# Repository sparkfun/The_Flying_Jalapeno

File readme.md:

The Flying Jalapeno
=======

This is a generic testbed board that will act as the "brain and usual hardware" for 99% of testbeds. We currently design a ton of testbeds using the pro mini, but this requires us to also put more circuitry on the testbed itself. Since we use basically the same extra stuff on every testbed, it makes sense to have a custom board that includes all of this.

It will be strictly used in QC and production (a sub assembly). 

The title "The Flying Jalapeno". I know I'm a dork, but hey, might as well name it something fun. And why not be in honor of the best AVC team name ever??

The extra hardware necessary for most testbeds:

-2 adjustable vregs with high-side switches
-2 resistor groups used for pre-testing for shorts to GND
-2 IOs setup for capsense (basically just 10M resistors for each "send" line)
-Resistors in place for PASS/FAIL leds
-Larger Vreg for VCC, to make more current available as needed
-Universal connector (2/18 header) that will mate with future pogobeds. (The idea here is that most future pogobeds will be comprised of two things: (2) the FLying Jalapeno and (2) the custom pogopin hardware.
-1x6 SMD FTDI RA header for easy programming and debug

License Information
-------------------

All of the designs in this repo are public domain but you buy me a beer if you use this and we meet someday ([Beerware license](http://en.wikipedia.org/wiki/Beerware)).

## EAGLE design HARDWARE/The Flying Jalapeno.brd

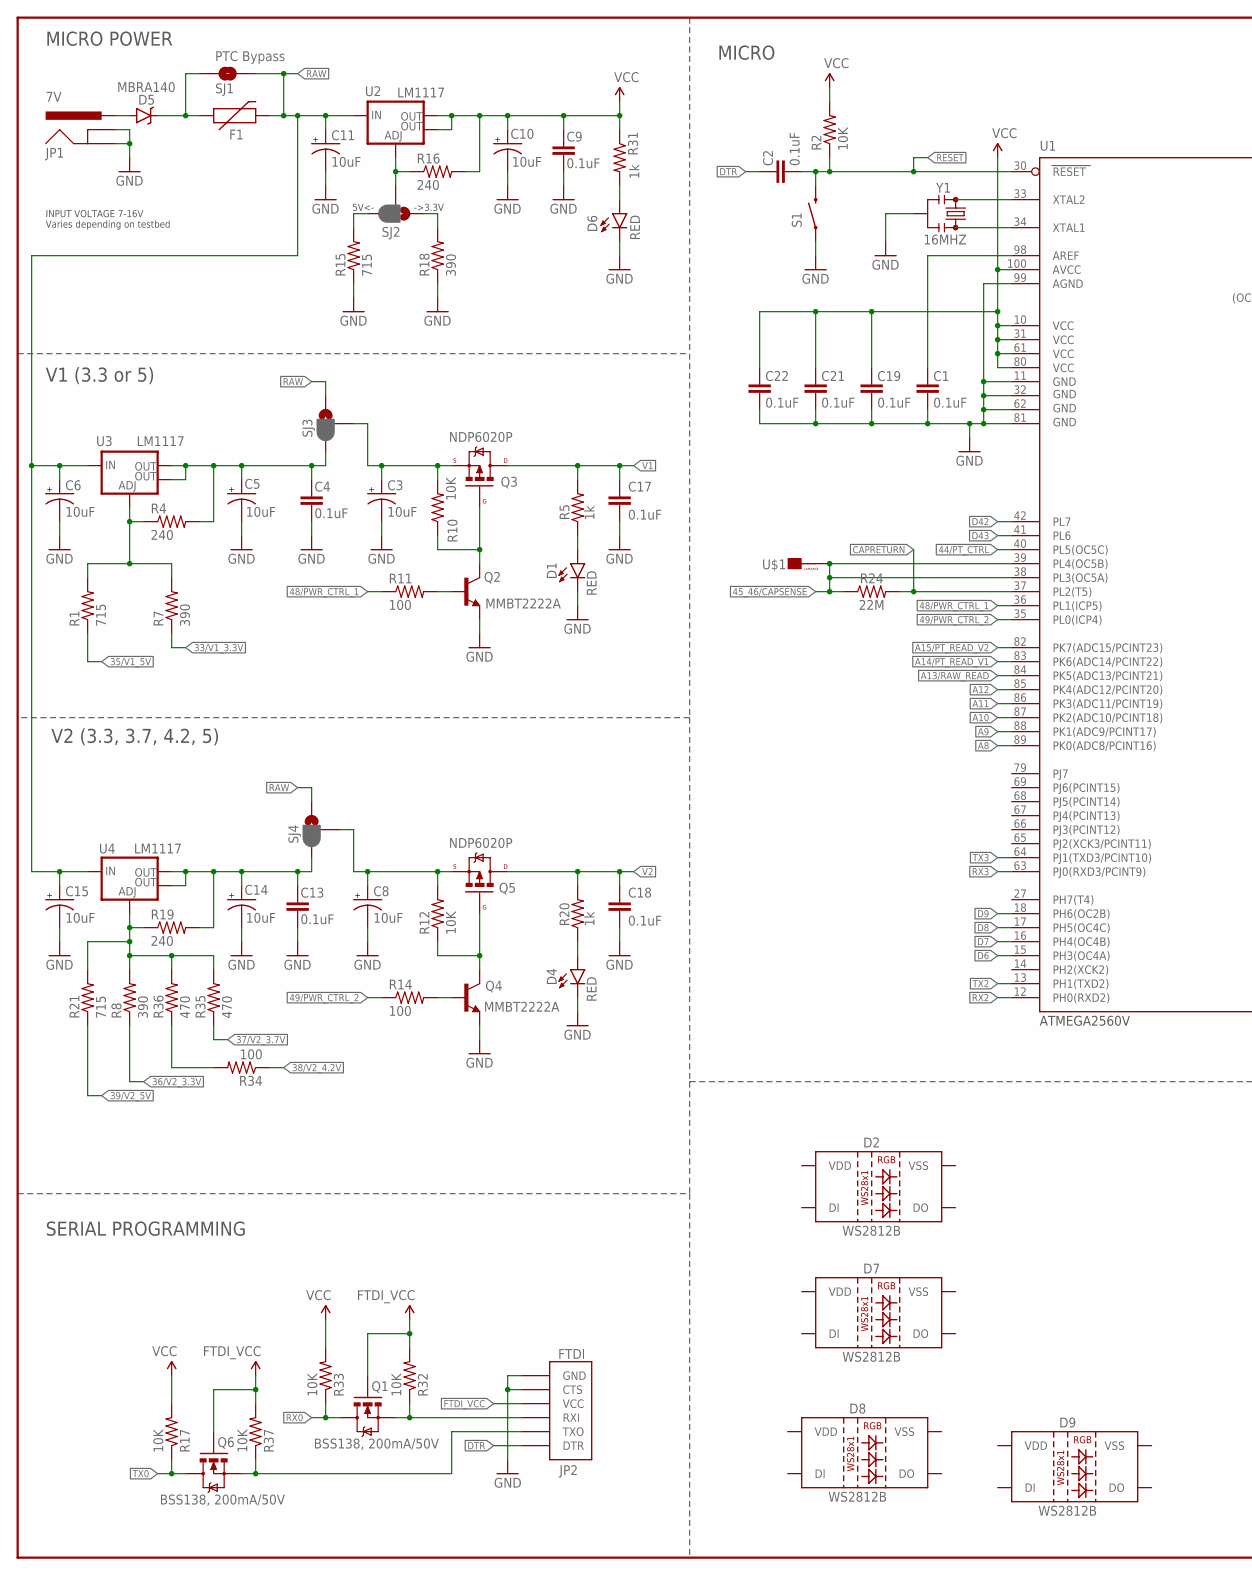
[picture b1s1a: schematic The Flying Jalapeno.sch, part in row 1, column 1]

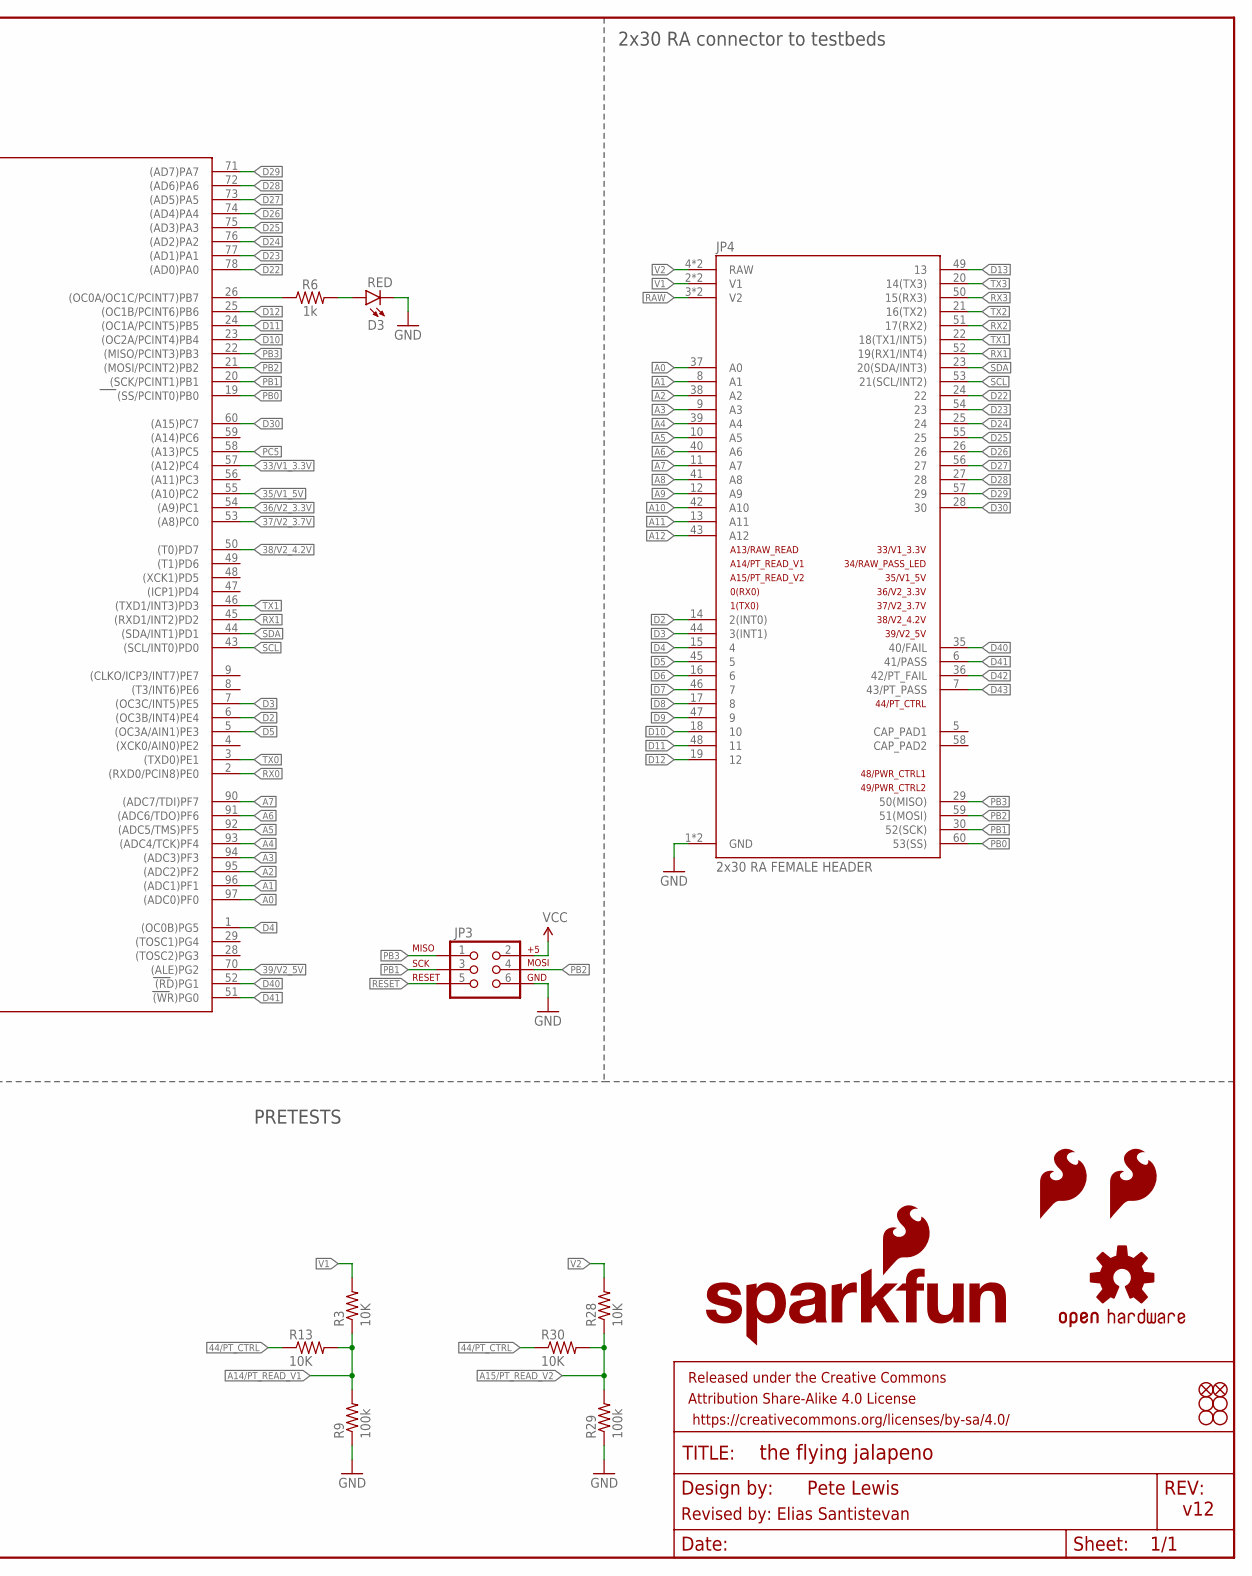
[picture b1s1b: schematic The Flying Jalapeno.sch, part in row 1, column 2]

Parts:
C1, C2, C4, C9, C13, C17, C18, C19, C21, C22: 0.1uF; 0603-CAP
C3, C8: 10uF; 0603-POLAR
C5, C6, C10, C11, C14, C15: 10uF; EIA3216@1
D1, D3, D4, D6: RED; LED-1206
D2, D7, D8, D9: WS2812B
D5: MBRA140; SMA-DIODE
F1: PTCTHERMISTOR1206; PTC-1206
FRAME1: FRAME-LEDGER; CREATIVE_COMMONS
JP1: 7V; POWER_JACK_PTH_LOCK
JP2: FTDI; FTDI_DEVICE_RA_SMT
JP3: AVR_SPI_PRG_6PTH; 2X3
JP4: 2x30 RA FEMALE HEADER; FLYING_JALAPENO_V3_F
JP5, JP8: FIDUCIALUFIDUCIAL; MICRO-FIDUCIAL
LOGO1: SFE_LOGO_NAME_FLAME.5_INCH; SFE_LOGO_NAME_FLAME_.5
LOGO2: SFE_LOGO_FLAME.3_INCH; SFE_LOGO_FLAME_.3
LOGO3: SFE_LOGO_FLAME.1_INCH; SFE_LOGO_FLAME_.1
LOGO4: OSHW-LOGOL; OSHW-LOGO-L
Q1, Q6: BSS138, 200mA/50V; SOT23-3
Q2, Q4: MMBT2222A; SOT23-3
Q3, Q5: NDP6020P; TO220V
R1, R15, R21: 715; 0603-RES
R2, R3, R10, R12, R13, R17, R28, R30, R32, R33, R37: 10K; 0603-RES
R4, R16, R19: 240; 0603-RES
R5, R6, R20, R31: 1k; 0603
R7, R8, R18: 390; 0603-RES
R9, R29: 100k; 0603-RES
R11, R14, R34: 100; 0603-RES
R24: 22M; 0603
R35, R36: 470; 0603-RES
S1: SWITCH-MOMENTARY-2SMD-REDUNDANT; TACTILE-SWITCH-SMD
SJ1: PTC Bypass; PAD-JUMPER-2-NO_NO_SILK
SJ2, SJ3, SJ4: JUMPER-PAD-3-2OF3_NC_BY_PASTE; PAD-JUMPER-3-2OF3_NC_BY_PASTE_YES_SILK_FULL_BOX
STANDOFF1, STANDOFF2, STANDOFF3, STANDOFF4: STAND-OFFTIGHT; STAND-OFF-TIGHT
U1: ATMEGA2560AU; TQFP100
U2, U3, U4: LM1117; SOT223
U$1: CAPSENSE_BUTTON_PAD_ONLY; CAPSENSE_BUTTON_PADS_ONLY
Y1: 16MHZ; RESONATOR-SMD

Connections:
33/V1_3.3V: R7.1, U1.57 ((A12)PC4)
35/V1_5V: R1.1, U1.55 ((A10)PC2)
36/V2_3.3V: R8.1, U1.54 ((A9)PC1)
37/V2_3.7V: R35.1, U1.53 ((A8)PC0)
38/V2_4.2V: R34.1, U1.50 ((T0)PD7)
39/V2_5V: R21.1, U1.70 ((ALE)PG2)
44/PT_CTRL: R13.1, R30.1, U1.40 (PL5(OC5C))
45_46/CAPSENSE: R24.1, U1.38 (PL3(OC5A)), U1.39 (PL4(OC5B)), U$1.CAPSENSE_PAD
48/PWR_CTRL_1: R11.1, U1.36 (PL1(ICP5))
49/PWR_CTRL_2: R14.1, U1.35 (PL0(ICP4))
A0: JP4.37 (A0), U1.97 ((ADC0)PF0)
A1: JP4.8 (A1), U1.96 ((ADC1)PF1)
A2: JP4.38 (A2), U1.95 ((ADC2)PF2)
A3: JP4.9 (A3), U1.94 ((ADC3)PF3)
A4: JP4.39 (A4), U1.93 ((ADC4/TCK)PF4)
A5: JP4.10 (A5), U1.92 ((ADC5/TMS)PF5)
A6: JP4.40 (A6), U1.91 ((ADC6/TDO)PF6)
A7: JP4.11 (A7), U1.90 ((ADC7/TDI)PF7)
A8: JP4.41 (A8), U1.89 (PK0(ADC8/PCINT16))
A9: JP4.12 (A9), U1.88 (PK1(ADC9/PCINT17))
A10: JP4.42 (A10), U1.87 (PK2(ADC10/PCINT18))
A11: JP4.13 (A11), U1.86 (PK3(ADC11/PCINT19))
A12: JP4.43 (A12), U1.85 (PK4(ADC12/PCINT20))
A13/RAW_READ: U1.84 (PK5(ADC13/PCINT21))
A14/PT_READ_V1: R3.1, R9.2, R13.2, U1.83 (PK6(ADC14/PCINT22))
A15/PT_READ_V2: R28.1, R29.2, R30.2, U1.82 (PK7(ADC15/PCINT23))
AREF: C1.2, U1.98 (AREF)
CAPRETURN: R24.2, U1.37 (PL2(T5))
D2: JP4.14 (2(INT0)), U1.6 ((OC3B/INT4)PE4)
D3: JP4.44 (3(INT1)), U1.7 ((OC3C/INT5)PE5)
D4: JP4.15 (4), U1.1 ((OC0B)PG5)
D5: JP4.45 (5), U1.5 ((OC3A/AIN1)PE3)
D6: JP4.16 (6), U1.15 (PH3(OC4A))
D7: JP4.46 (7), U1.16 (PH4(OC4B))
D8: JP4.17 (8), U1.17 (PH5(OC4C))
D9: JP4.47 (9), U1.18 (PH6(OC2B))
D10: JP4.18 (10), U1.23 ((OC2A/PCINT4)PB4)
D11: JP4.48 (11), U1.24 ((OC1A/PCINT5)PB5)
D12: JP4.19 (12), U1.25 ((OC1B/PCINT6)PB6)
D13: JP4.49 (13), R6.1, U1.26 ((OC0A/OC1C/PCINT7)PB7)
D22: JP4.24 (22), U1.78 ((AD0)PA0)
D23: JP4.54 (23), U1.77 ((AD1)PA1)
D24: JP4.25 (24), U1.76 ((AD2)PA2)
D25: JP4.55 (25), U1.75 ((AD3)PA3)
D26: JP4.26, U1.74 ((AD4)PA4)
D27: JP4.56 (27), U1.73 ((AD5)PA5)
D28: JP4.27 (28), U1.72 ((AD6)PA6)
D29: JP4.57 (29), U1.71 ((AD7)PA7)
D30: JP4.28 (30), U1.60 ((A15)PC7)
D40: JP4.35 (40/FAIL), U1.52 ((RD)PG1)
D41: JP4.6 (41/PASS), U1.51 ((WR)PG0)
D42: JP4.36 (42/PT_FAIL), U1.42 (PL7)
D43: JP4.7 (43/PT_PASS), U1.41 (PL6)
DTR: C2.2, JP2.1 (DTR)
FTDI_VCC: JP2.4 (VCC), Q1.1 (G), Q6.1 (G), R32.2, R37.2
GND: C1.1, C3.-, C4.2, C5.C (-), C6.C (-), C8.-, C9.2, C10.C (-), C11.C (-), C13.2, C14.C (-), C15.C (-), C17.2, C18.2, C19.1, C21.1, C22.1, D1.C, D3.C, D4.C, D6.C, JP1.GND, JP1.GNDBREAK, JP2.5 (CTS), JP2.6 (GND), JP3.6, JP4.1 (GND), JP4.31 (GND), Q2.2 (E), Q4.2 (E), R9.1, R15.1, R18.1, R29.1, S1.1, S1.2 (1), U1.11 (GND), U1.32 (GND1), U1.62 (GND2), U1.81 (GND3), U1.99 (AGND), Y1.2
unnamed: R34.2, R36.1
unnamed: R16.1, SJ2.2, U2.1 (ADJ)
unnamed: D3.A, R6.2
unnamed: D1.A, R5.1
unnamed: Q2.1 (B), R11.2
unnamed: R1.2, R4.1, R7.2, U3.1 (ADJ)
unnamed: R8.2, R19.1, R21.2, R35.2, R36.2, U4.1 (ADJ)
unnamed: D4.A, R20.1
unnamed: Q2.3 (C), Q3.1 (G), R10.1
unnamed: Q4.1 (B), R14.2
unnamed: Q4.3 (C), Q5.1 (G), R12.1
unnamed: D5.C, F1.1, SJ1.1
unnamed: JP2.3 (RXI), Q1.2 (S), R32.1
unnamed: R18.2, SJ2.1
unnamed: R15.2, SJ2.3
unnamed: C4.1, C5.A (+), R4.2, SJ3.3, U3.2 (OUT), U3.4 (OUT)
unnamed: C3.+, Q3.3 (S), R10.2, SJ3.2
unnamed: C8.+, Q5.3 (S), R12.2, SJ4.2
unnamed: D5.A, JP1.PWR
unnamed: D6.A, R31.2
unnamed: JP2.2 (TXO), Q6.2 (S), R37.1
unnamed: U1.33 (XTAL2), Y1.3
unnamed: U1.34 (XTAL1), Y1.1
PB0: JP4.60 (53(SS)), U1.19 ((SS/PCINT0)PB0)
PB1: JP3.3, JP4.30 (52(SCK)), U1.20 ((SCK/PCINT1)PB1)
PB2: JP3.4, JP4.59 (51(MOSI)), U1.21 ((MOSI/PCINT2)PB2)
PB3: JP3.1, JP4.29 (50(MISO)), U1.22 ((MISO/PCINT3)PB3)
PC5: U1.58 ((A13)PC5)
RAW: C6.A (+), C11.A (+), C15.A (+), F1.2, JP4.3 (V2), JP4.33 (V2), SJ1.2, SJ3.1, SJ4.1, U2.3 (IN), U3.3 (IN), U4.3 (IN)
RESET: C2.1, JP3.5, R2.1, S1.3 (2), S1.4 (2), U1.30 (RESET)
RX0: Q1.3 (D), R33.1, U1.2 ((RXD0/PCIN8)PE0)
RX1: JP4.52 (19(RX1/INT4)), U1.45 ((RXD1/INT2)PD2)
RX2: JP4.51 (17(RX2)), U1.12 (PH0(RXD2))
RX3: JP4.50 (15(RX3)), U1.63 (PJ0(RXD3/PCINT9))
SCL: JP4.53 (21(SCL/INT2)), U1.43 ((SCL/INT0)PD0)
SDA: JP4.23 (20(SDA/INT3)), U1.44 ((SDA/INT1)PD1)
TX0: Q6.3 (D), R17.1, U1.3 ((TXD0)PE1)
TX1: JP4.22 (18(TX1/INT5)), U1.46 ((TXD1/INT3)PD3)
TX2: JP4.21 (16(TX2)), U1.13 (PH1(TXD2))
TX3: JP4.20 (14(TX3)), U1.64 (PJ1(TXD3/PCINT10))
V1: C17.1, JP4.2 (V1), JP4.32 (V1), Q3.2 (D), R3.2, R5.2
V2: C18.1, JP4.4 (RAW), JP4.34 (RAW), Q5.2 (D), R20.2, R28.2
VCC: C9.1, C10.A (+), C19.2, C21.2, C22.2, JP3.2, R2.2, R16.2, R17.2, R31.1, R33.2, U1.10 (VCC), U1.31 (VCC1), U1.61 (VCC2), U1.80 (VCC3), U1.100 (AVCC), U2.2 (OUT), U2.4 (OUT)
VREG2OUT: C13.1, C14.A (+), R19.2, SJ4.3, U4.2 (OUT), U4.4 (OUT)

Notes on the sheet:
PRETESTS
MICRO POWER
V1 (3.3 or 5)
V2 (3.3, 3.7, 4.2, 5)
SERIAL PROGRAMMING
MICRO
Pete Lewis
v12
ATMEGA2560V
2x30 RA connector to testbeds
INPUT VOLTAGE 7-16V Varies depending on testbed
->3.3V
5V<-
Revised by: Elias Santistevan

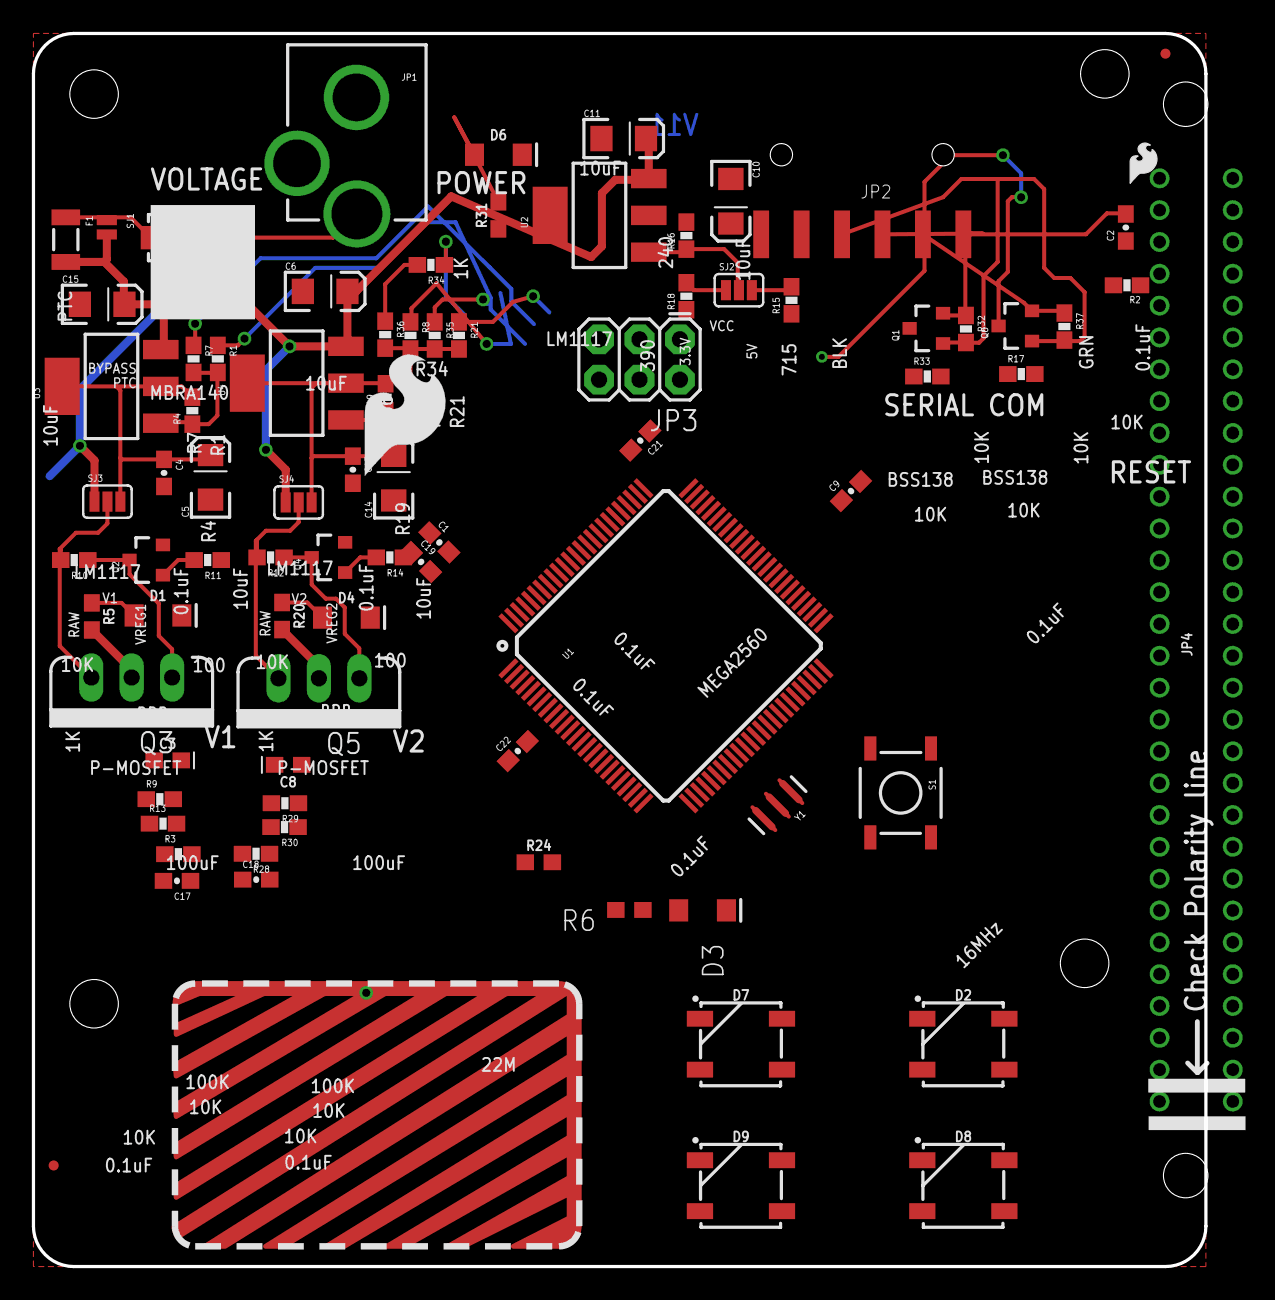
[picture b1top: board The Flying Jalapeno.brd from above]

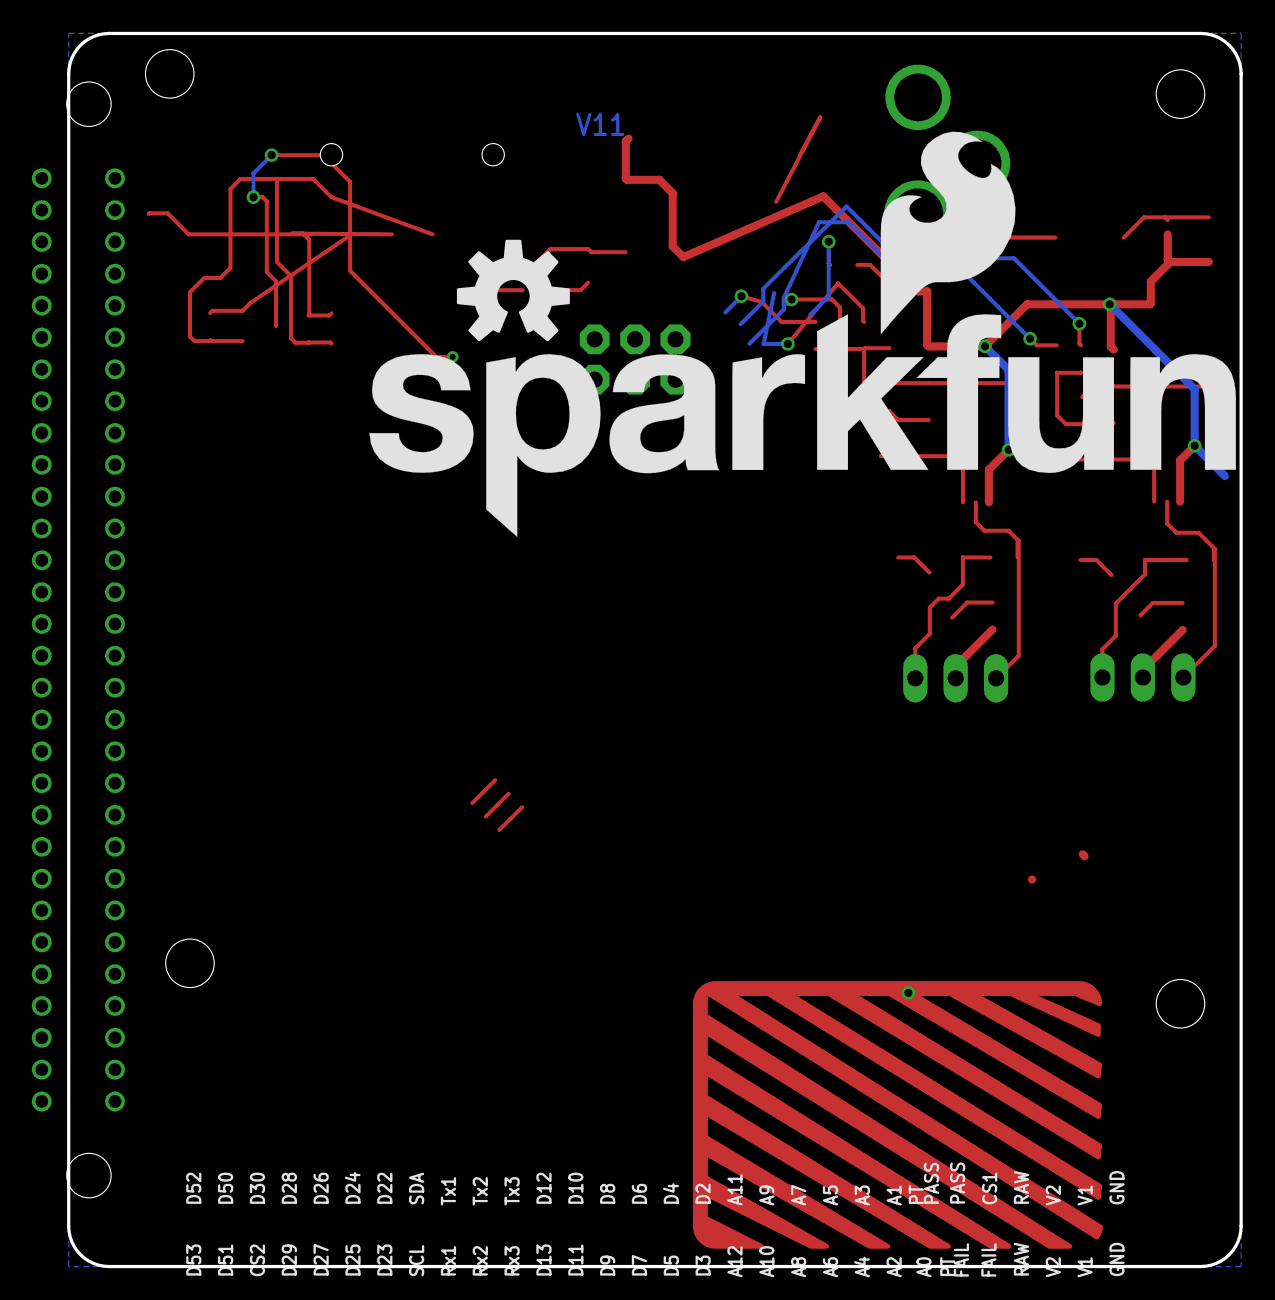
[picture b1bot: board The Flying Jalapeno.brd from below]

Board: 2 copper layers, 73.7 x 77.5 mm, 92 parts (2 on the bottom side), 98 nets.

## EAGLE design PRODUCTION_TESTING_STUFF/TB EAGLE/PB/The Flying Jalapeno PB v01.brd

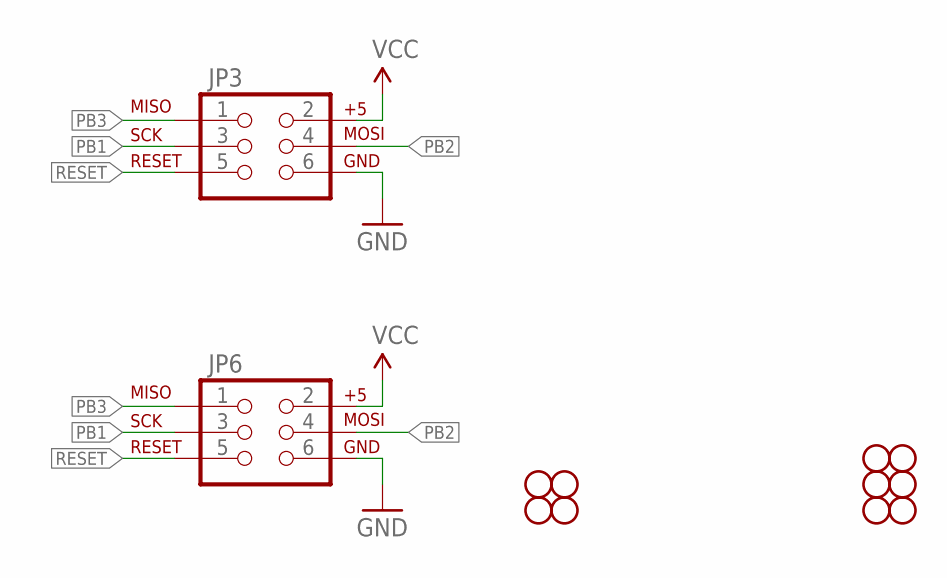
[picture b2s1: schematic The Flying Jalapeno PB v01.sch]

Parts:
JP3, JP6: AVR_SPI_PRG_6PTH; 2X3
STANDOFF1, STANDOFF2, STANDOFF3, STANDOFF4, STANDOFF5, STANDOFF6, STANDOFF7, STANDOFF8, STANDOFF9, STANDOFF10: STAND-OFFTIGHT; STAND-OFF-TIGHT

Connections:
GND: JP3.6, JP6.6
PB1: JP3.3, JP6.3
PB2: JP3.4, JP6.4
PB3: JP3.1, JP6.1
RESET: JP3.5, JP6.5
VCC: JP3.2, JP6.2

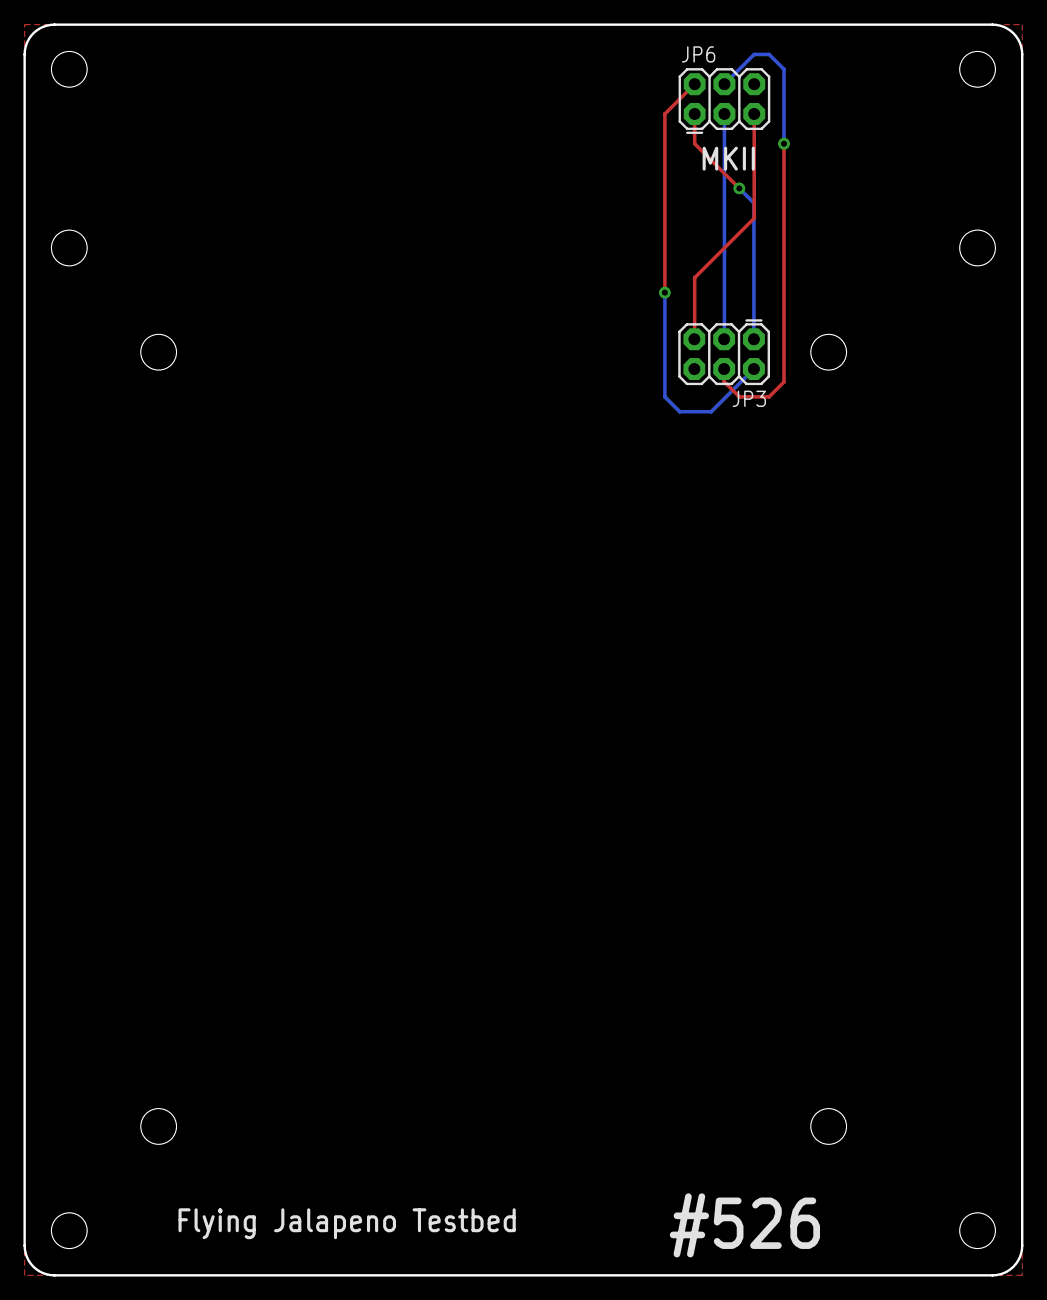
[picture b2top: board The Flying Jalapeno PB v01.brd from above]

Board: 2 copper layers, 85.1 x 106.7 mm, 12 parts (0 on the bottom side), 6 nets.

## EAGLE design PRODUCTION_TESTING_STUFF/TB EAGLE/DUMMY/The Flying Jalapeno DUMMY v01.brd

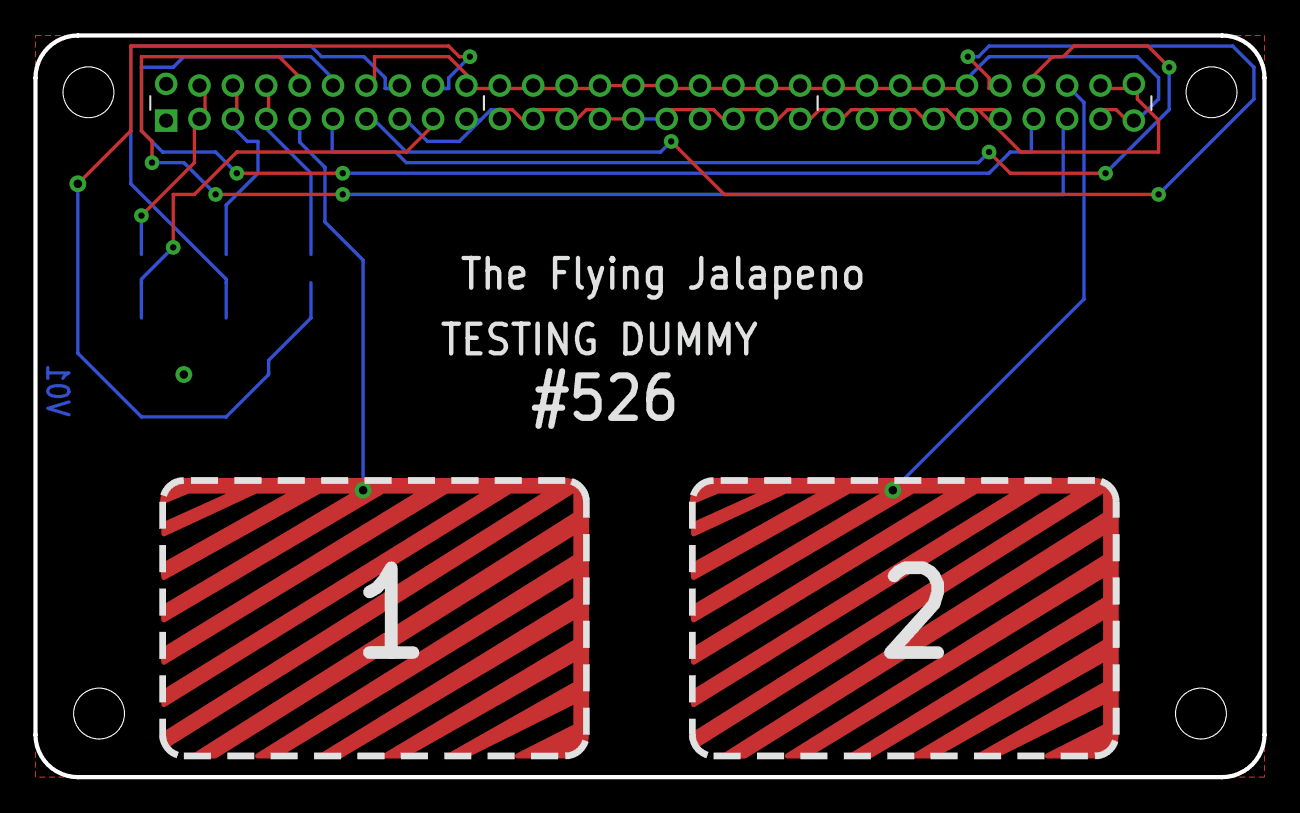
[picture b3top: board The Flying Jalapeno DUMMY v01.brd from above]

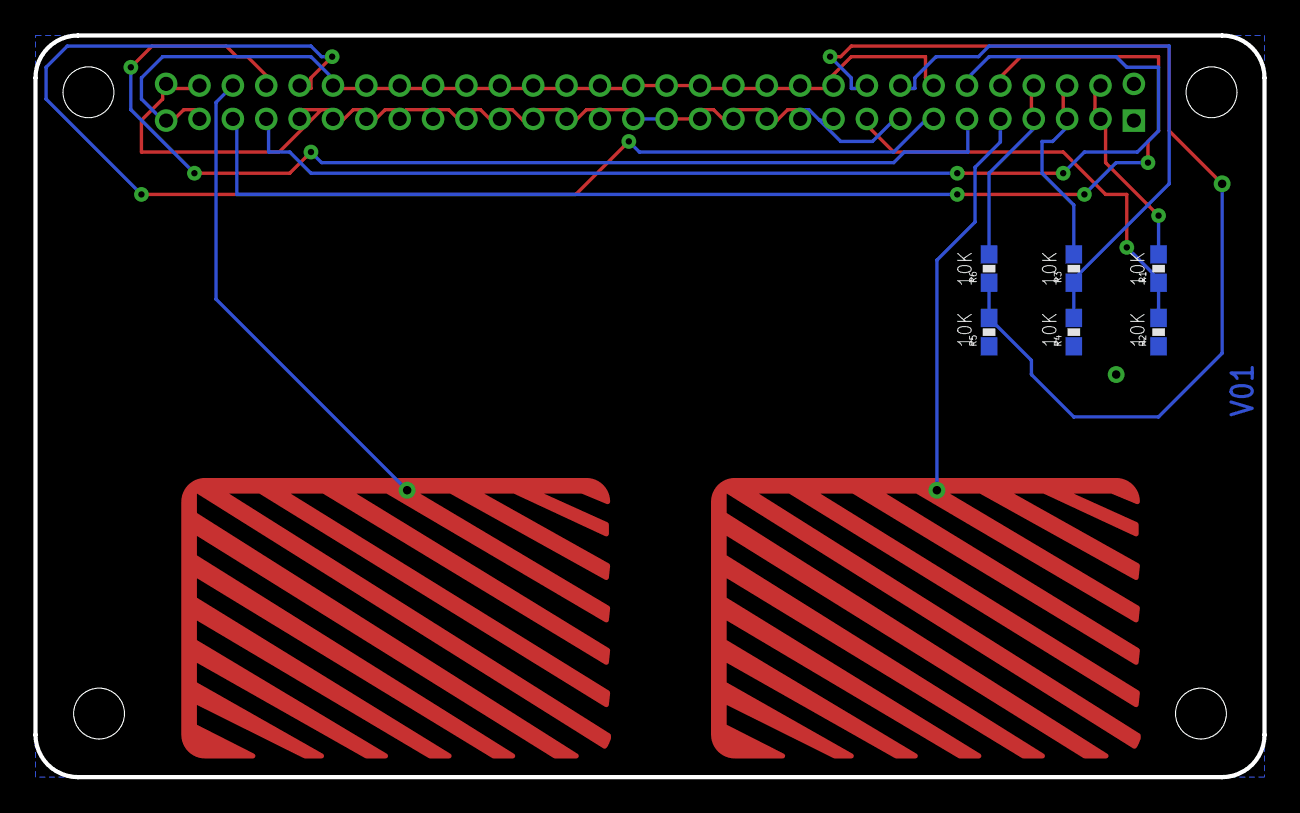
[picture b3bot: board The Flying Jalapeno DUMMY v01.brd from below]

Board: 2 copper layers, 73.7 x 44.5 mm, 11 parts (6 on the bottom side), 15 nets.

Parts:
CS1, CS2: CAPSENSE_BUTTON_PAD_ONLY; CAPSENSE_BUTTON_PADS_ONLY
JP6: FLYING_JALAPENO_V2MALE; FLYING_JALAPENO_V2_M
R1, R2, R3, R4, R5, R6: 10K; 0603-RES
STANDOFF1, STANDOFF2: STAND-OFFTIGHT; STAND-OFF-TIGHT

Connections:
GND: JP6.1, JP6.31, R2.1, R4.1, R5.1
unnamed: JP6.39, R5.2, R6.1
unnamed: JP6.4, JP6.34, R6.2
unnamed: CS2.CAPSENSE_PAD, JP6.58
unnamed: CS1.CAPSENSE_PAD, JP6.5
unnamed: JP6.2, JP6.32, R1.2
unnamed: JP6.9, R1.1, R2.2
unnamed: JP6.3, JP6.33, R3.2
unnamed: JP6.38, R3.1, R4.2
unnamed: JP6.28, JP6.35
unnamed: JP6.6, JP6.57
unnamed: JP6.27, JP6.36
unnamed: JP6.7, JP6.56
NET1: JP6.29, JP6.30, JP6.37, JP6.40, JP6.41, JP6.42, JP6.43, JP6.44, JP6.45, JP6.46, JP6.47, JP6.48, JP6.49, JP6.50, JP6.51, JP6.52, JP6.53, JP6.54, JP6.55
NET2: JP6.8, JP6.10, JP6.11, JP6.12, JP6.13, JP6.14, JP6.15, JP6.16, JP6.17, JP6.18, JP6.19, JP6.20, JP6.21, JP6.22, JP6.23, JP6.24, JP6.25, JP6.26, JP6.59, JP6.60

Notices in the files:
parts and their libraries:
SparkFun-Passives: Licensing: CC v3.0 Share-Alike You are welcome to use this library for commercial purposes.
SparkFun-Aesthetics: Licensing: Creative Commons ShareAlike 4.0 International - https://creativecommons.org/licenses/by-sa/4.0
SparkFun-Aesthetics: Released under the Creative Commons
